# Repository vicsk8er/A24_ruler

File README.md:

# CCI UdeS A24_ruler  
Concours de Circuit Imprimé Université de Sherbrooke, automne 2024  
## Thème : règle

Bienvenue à la compétition de conception de PCB sur le thème "règle" ! Cette compétition vise à stimuler la créativité et l'innovation dans la conception de circuits imprimés en vous invitant à créer une souris d'ordinateur unique et fonctionnelle.

### Répertoire "Template"  
Le répertoire "Template" contient tous les documents à remplir pour participer à la compétition. Vous y trouverez :  
- Formulaire d'idée  
- Formulaire d'inscription  

Le répertoire contient également un "Template" pour vous aider lors de la création de la documentation :  
- TEMPLATES de documentation CCI  

### Répertoires code, elec et mech  
Chacun de ces répertoires contient de la documentation de départ pour vous guider. Consultez la section "doc". Ces répertoires sont également là pour vous aider à vous organiser lors du développement de votre règle.

### Comment forker le dépôt

1. Accédez au dépôt GitHub officiel à l'adresse suivante : `https://github.com/CCI-udes/A24_ruler`.
2. Cliquez sur le bouton "Fork" en haut à droite de la page du dépôt.
3. Sélectionnez votre propre compte GitHub comme destination du fork.
4. Clonez le dépôt forké sur votre machine locale en utilisant la commande suivante :
   ```bash
   git clone https://github.com/<votre-utilisateur>/A24_ruler.git
   ```

### Ressources supplémentaires

- Si vous avez des questions ou avez besoin d'aide, n'hésitez pas à nous contacter.
- Rejoignez notre canal Discord pour discuter avec d'autres participants et obtenir des conseils et des astuces.

Nous vous souhaitons bonne chance et avons hâte de voir vos créations !

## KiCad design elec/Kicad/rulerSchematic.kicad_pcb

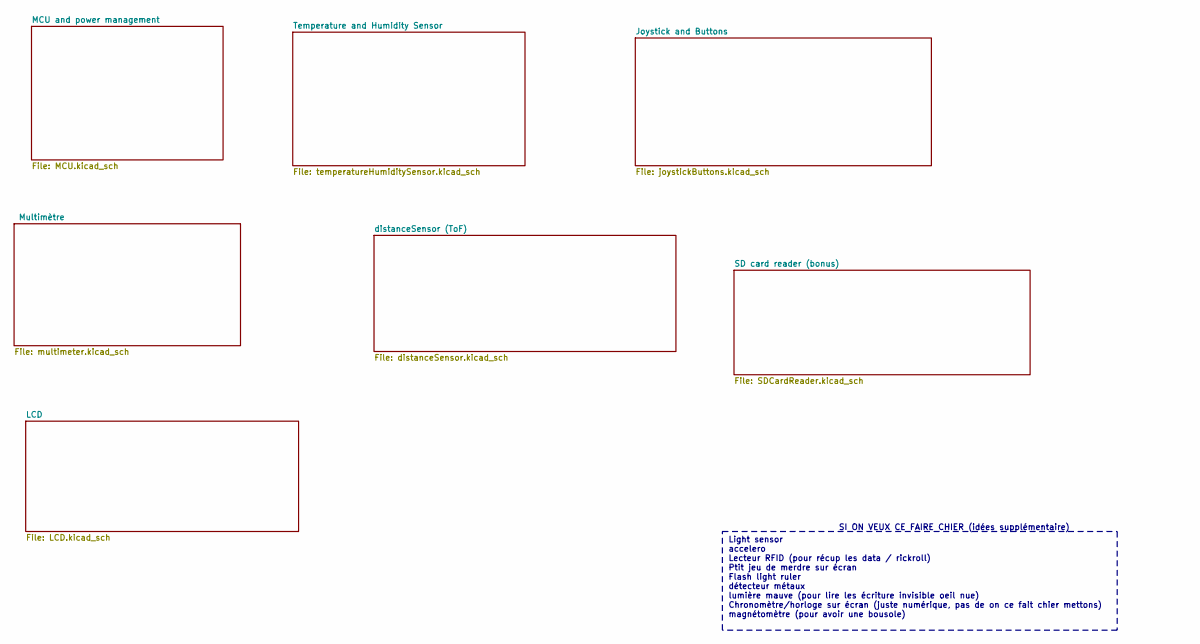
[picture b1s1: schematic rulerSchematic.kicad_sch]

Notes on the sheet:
Light sensor accelero Lecteur RFID (pour récup les data / rickroll) Ptit jeu de merdre sur écran Flash light ruler détecteur métaux lumière mauve (pour lire les écriture invisible oeil nue) Chronomètre/horloge sur écran (juste numérique, pas de on ce fait chier mettons) magnétomètre (pour avoir une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
SI ON VEUX CE FAIRE CHIER (idées supplémentaire)

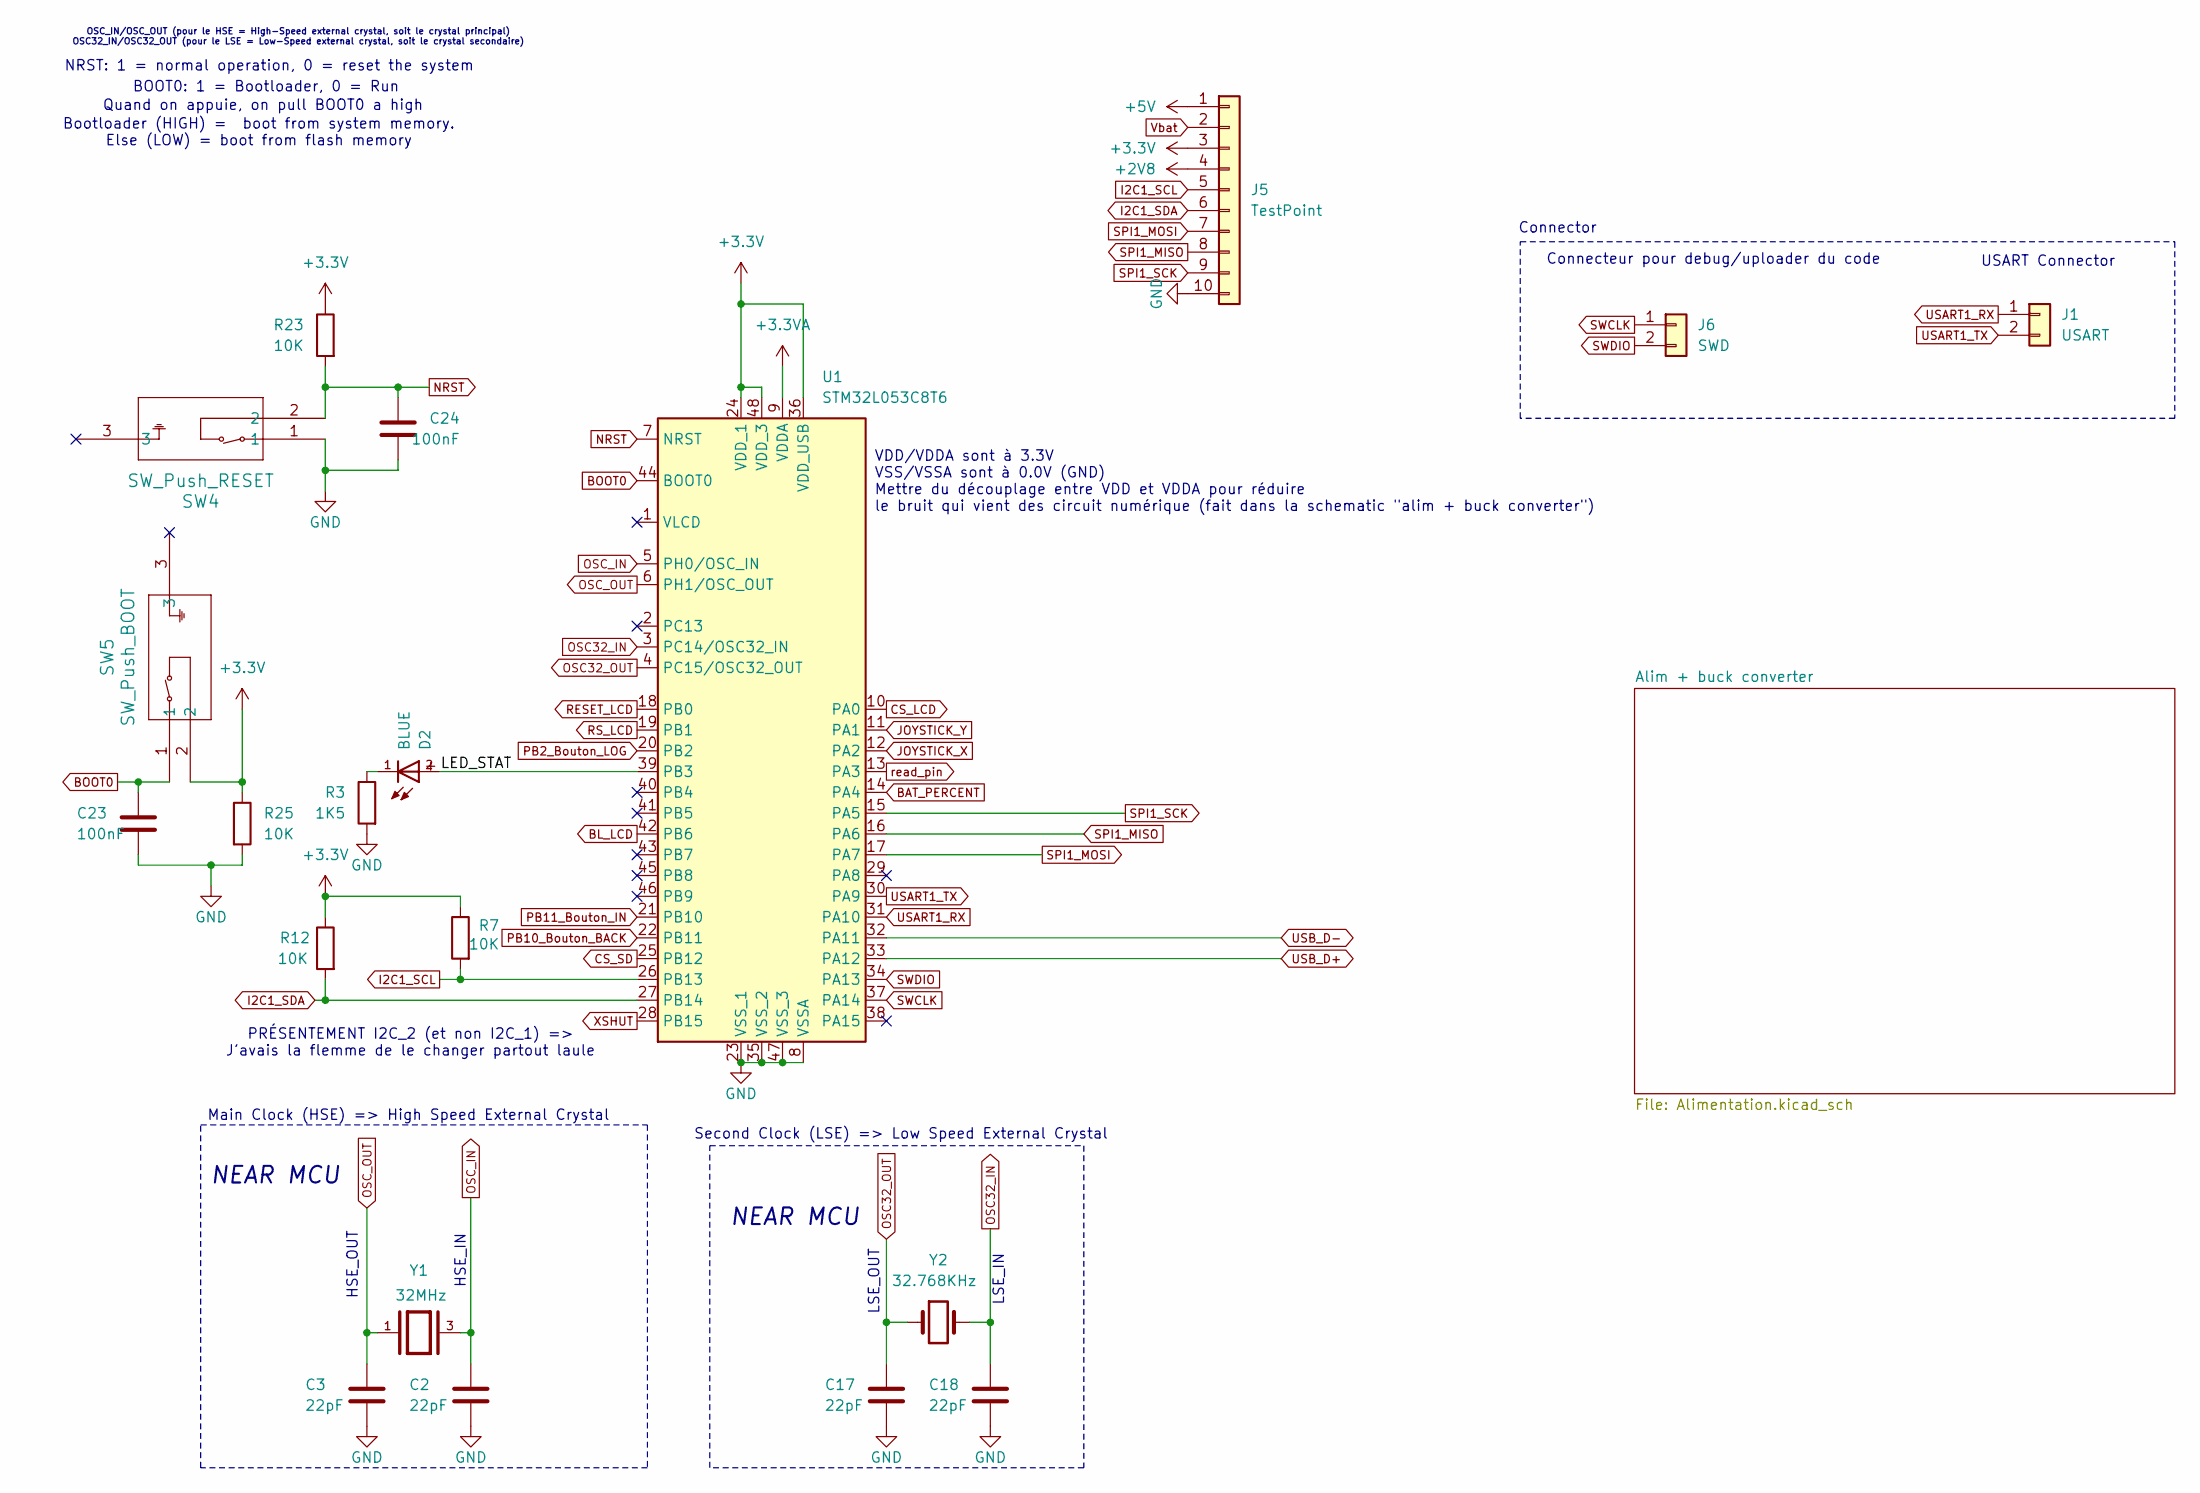
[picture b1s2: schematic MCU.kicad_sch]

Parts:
C2, C3, C17, C18: 22pF; C_0402_1005Metric_Pad0.74x0.62mm_HandSolder
C23, C24: 100nF; C_0402_1005Metric_Pad0.74x0.62mm_HandSolder
D2: BLUE; WL-SMCD_0603
J1: USART; PinHeader_1x02_P2.54mm_Vertical
J5: TestPoint; PinSocket_1x10_P2.54mm_Vertical
J6: SWD; PinHeader_1x02_P2.54mm_Vertical
R3: 1K5; R_0402_1005Metric_Pad0.72x0.64mm_HandSolder
R7, R12, R23, R25: 10K; R_0402_1005Metric_Pad0.72x0.64mm_HandSolder
SW4: SW_Push_RESET; B3U-1100P_OMR
SW5: SW_Push_BOOT; B3U-1100P_OMR
U1: STM32L053C8T6; LQFP-48_7x7mm_P0.5mm
Y1: 32MHz; OSC_XRCGB32M000F2P01R0; PARTREV N/A
Y2: 32.768KHz; Crystal_SMD_3215-2Pin_3.2x1.5mm

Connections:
+2V8: J5.4; also elsewhere on the board
+3.3V: J5.3, R7.1, R12.1, R23.1, R25.1, SW5.2, U1.24 (VDD_1), U1.36 (VDD_USB), U1.48 (VDD_3); also elsewhere on the board
+3.3VA: U1.9 (VDDA); also elsewhere on the board
+5V: J5.1; also elsewhere on the board
/MCU and power management/LED_STAT: D2.2, U1.39 (PB3)
BAT_PERCENT: U1.14 (PA4); also elsewhere on the board
BL_LCD: U1.42 (PB6); also elsewhere on the board
BOOT0: C23.1, SW5.1, U1.44 (BOOT0)
CS_LCD: U1.10 (PA0); also elsewhere on the board
CS_SD: U1.25 (PB12); also elsewhere on the board
GND: C2.2, C3.2, C17.2, C18.2, C23.2, C24.2, J5.10, R3.2, R25.2, SW4.1, U1.8 (VSSA), U1.23 (VSS_1), U1.35 (VSS_2), U1.47 (VSS_3); also elsewhere on the board
I2C1_SCL: J5.5, R7.2, U1.26 (PB13); also elsewhere on the board
I2C1_SDA: J5.6, R12.2, U1.27 (PB14); also elsewhere on the board
JOYSTICK_X: U1.12 (PA2); also elsewhere on the board
JOYSTICK_Y: U1.11 (PA1); also elsewhere on the board
NRST: C24.1, R23.2, SW4.2, U1.7 (NRST)
unnamed: D2.1, R3.1
OSC32_IN: C18.1, U1.3 (PC14/OSC32_IN), Y2.2
OSC32_OUT: C17.1, U1.4 (PC15/OSC32_OUT), Y2.1
OSC_IN: C2.1, U1.5 (PH0/OSC_IN), Y1.3
OSC_OUT: C3.1, U1.6 (PH1/OSC_OUT), Y1.1
PB2_Bouton_LOG: U1.20 (PB2); also elsewhere on the board
PB10_Bouton_BACK: U1.22 (PB11); also elsewhere on the board
PB11_Bouton_IN: U1.21 (PB10); also elsewhere on the board
RESET_LCD: U1.18 (PB0); also elsewhere on the board
RS_LCD: U1.19 (PB1); also elsewhere on the board
SPI1_MISO: J5.8, U1.16 (PA6); also elsewhere on the board
SPI1_MOSI: J5.7, U1.17 (PA7); also elsewhere on the board
SPI1_SCK: J5.9, U1.15 (PA5); also elsewhere on the board
SWCLK: J6.1, U1.37 (PA14)
SWDIO: J6.2, U1.34 (PA13)
USART1_RX: J1.1, U1.31 (PA10)
USART1_TX: J1.2, U1.30 (PA9)
USB_D+: U1.33 (PA12); also elsewhere on the board
USB_D-: U1.32 (PA11); also elsewhere on the board
Vbat: J5.2; also elsewhere on the board
XSHUT: U1.28 (PB15); also elsewhere on the board
read_pin: U1.13 (PA3); also elsewhere on the board

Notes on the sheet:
HSE_IN
BOOT0: 1 = Bootloader, 0 = Run
Connecteur pour debug/uploader du code
Main Clock (HSE) => High Speed External Crystal
Bootloader (HIGH) = boot from system memory. Else (LOW) = boot from flash memory
PRÉSENTEMENT I2C_2 (et non I2C_1) => J'avais la flemme de le changer partout laule
Second Clock (LSE) => Low Speed External Crystal
Quand on appuie, on pull BOOT0 a high
NEAR MCU
OSC_IN/OSC_OUT (pour le HSE = High-Speed external crystal, soit le crystal principal) OSC32_IN/OSC32_OUT (pour le LSE = Low-Speed external crystal, soit le crystal secondaire)
VDD/VDDA sont à 3.3V VSS/VSSA sont à 0.0V (GND) Mettre du découplage entre VDD et VDDA pour réduire le bruit qui vient des circuit numérique (fait dans la schematic "alim + buck converter")
Connector
NRST: 1 = normal operation, 0 = reset the system
USART Connector
LSE_IN
LSE_OUT
HSE_OUT

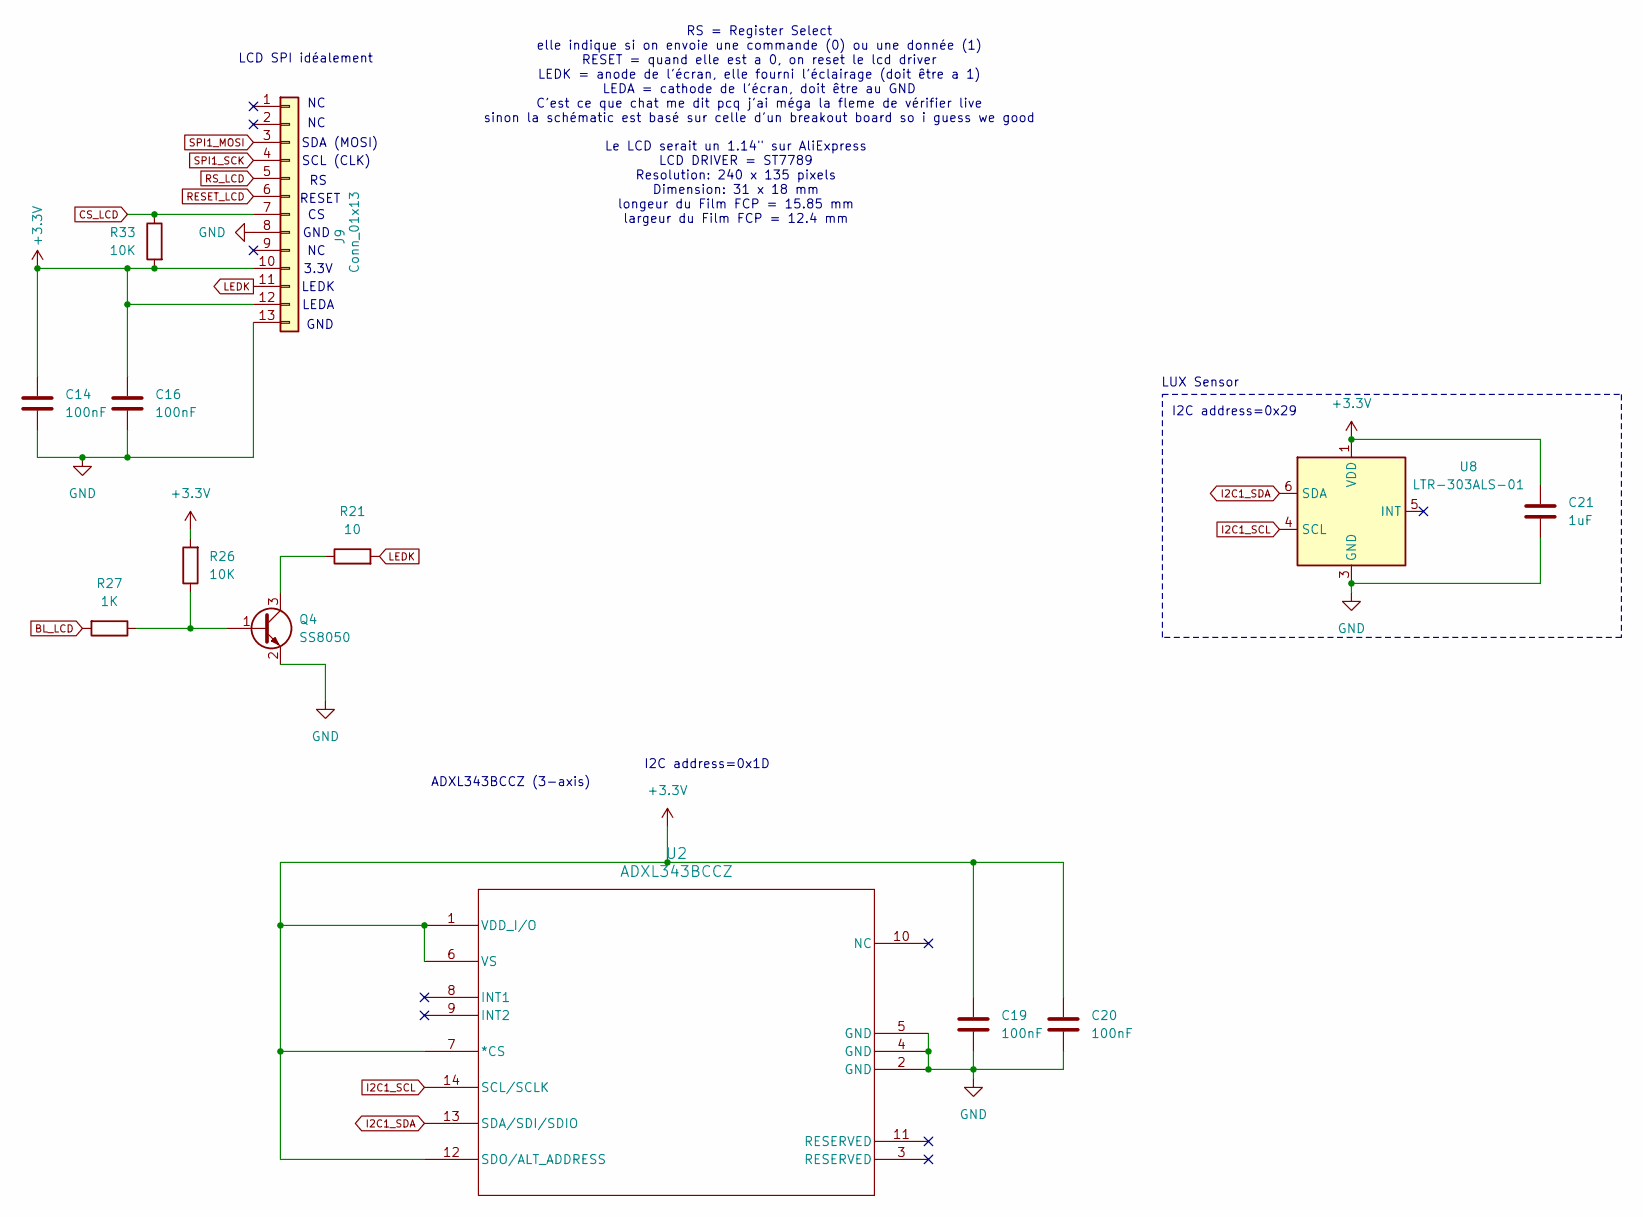
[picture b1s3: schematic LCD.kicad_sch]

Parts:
C14, C16, C19, C20: 100nF; C_0402_1005Metric_Pad0.74x0.62mm_HandSolder
C21: 1uF; C_0402_1005Metric_Pad0.74x0.62mm_HandSolder
J9: Conn_01x13; Hirose_FH12-13S-0.5SH_1x13-1MP_P0.50mm_Horizontal
Q4: SS8050; SOT-23
R21: 10; R_0402_1005Metric_Pad0.72x0.64mm_HandSolder
R26, R33: 10K; R_0402_1005Metric_Pad0.72x0.64mm_HandSolder
R27: 1K; R_0402_1005Metric_Pad0.72x0.64mm_HandSolder
U2: ADXL343BCCZ; LGA_CC-14-1_ADI
U8: LTR-303ALS-01; Lite-On_LTR-303ALS-01

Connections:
+3.3V: C14.1, C16.1, C19.1, C20.1, C21.1, J9.10, J9.12, R26.2, R33.2, U2.1 (VDD_I/O), U2.6 (VS), U2.7 (*CS), U2.12 (SDO/ALT_ADDRESS), U8.1 (VDD); also elsewhere on the board
BL_LCD: R27.2; also elsewhere on the board
CS_LCD: J9.7, R33.1; also elsewhere on the board
GND: C14.2, C16.2, C19.2, C20.2, C21.2, J9.8, J9.13, Q4.2 (E), U2.2 (GND), U2.4 (GND), U2.5 (GND), U8.3 (GND); also elsewhere on the board
I2C1_SCL: U2.14 (SCL/SCLK), U8.4 (SCL); also elsewhere on the board
I2C1_SDA: U2.13 (SDA/SDI/SDIO), U8.6 (SDA); also elsewhere on the board
LEDK: J9.11, R21.2
unnamed: Q4.1 (B), R26.1, R27.1
unnamed: Q4.3 (C), R21.1
RESET_LCD: J9.6; also elsewhere on the board
RS_LCD: J9.5; also elsewhere on the board
SPI1_MOSI: J9.3; also elsewhere on the board
SPI1_SCK: J9.4; also elsewhere on the board

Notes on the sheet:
RESET
LEDA
GND
LEDK
SCL (CLK)
LUX Sensor
ADXL343BCCZ (3-axis)
SDA (MOSI)
RS = Register Select elle indique si on envoie une commande (0) ou une donnée (1) RESET = quand elle est a 0, on reset le lcd driver LEDK = anode de l'écran, elle fourni l'éclairage (doit être a 1) LEDA = cathode de l'écran, doit être au GND C'est ce que chat me dit pcq j'ai méga la fleme de vérifi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
LCD SPI idéalement
I2C address=0x1D
3.3V
I2C address=0x29
Le LCD serait un 1.14" sur AliExpress LCD DRIVER = ST7789 Resolution: 240 x 135 pixels Dimension: 31 x 18 mm longeur du Film FCP = 15.85 mm largeur du Film FCP = 12.4 mm

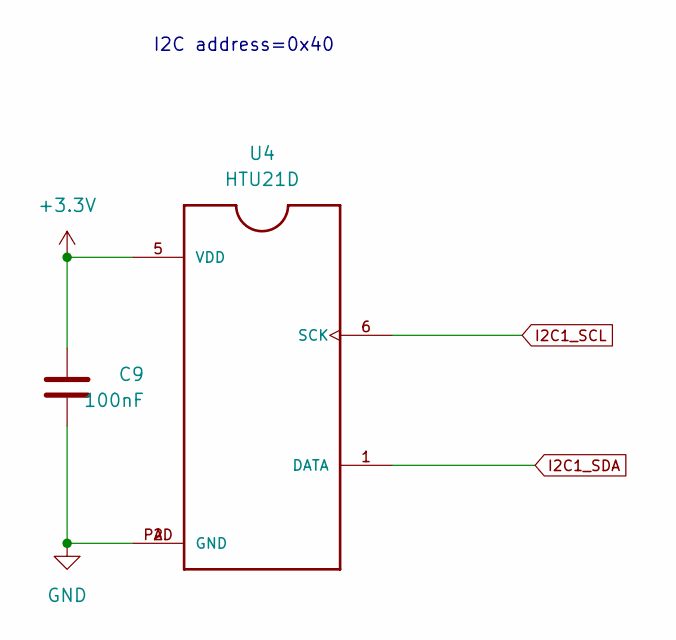
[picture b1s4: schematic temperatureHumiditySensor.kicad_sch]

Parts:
C9: 100nF; C_0402_1005Metric_Pad0.74x0.62mm_HandSolder
U4: HTU21D; QFN100P300X300X100-7N

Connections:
+3.3V: C9.1, U4.5 (VDD); also elsewhere on the board
GND: C9.2, U4.2 (GND), U4.PAD (GND); also elsewhere on the board
I2C1_SCL: U4.6 (SCK); also elsewhere on the board
I2C1_SDA: U4.1 (DATA); also elsewhere on the board

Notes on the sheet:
I2C address=0x40

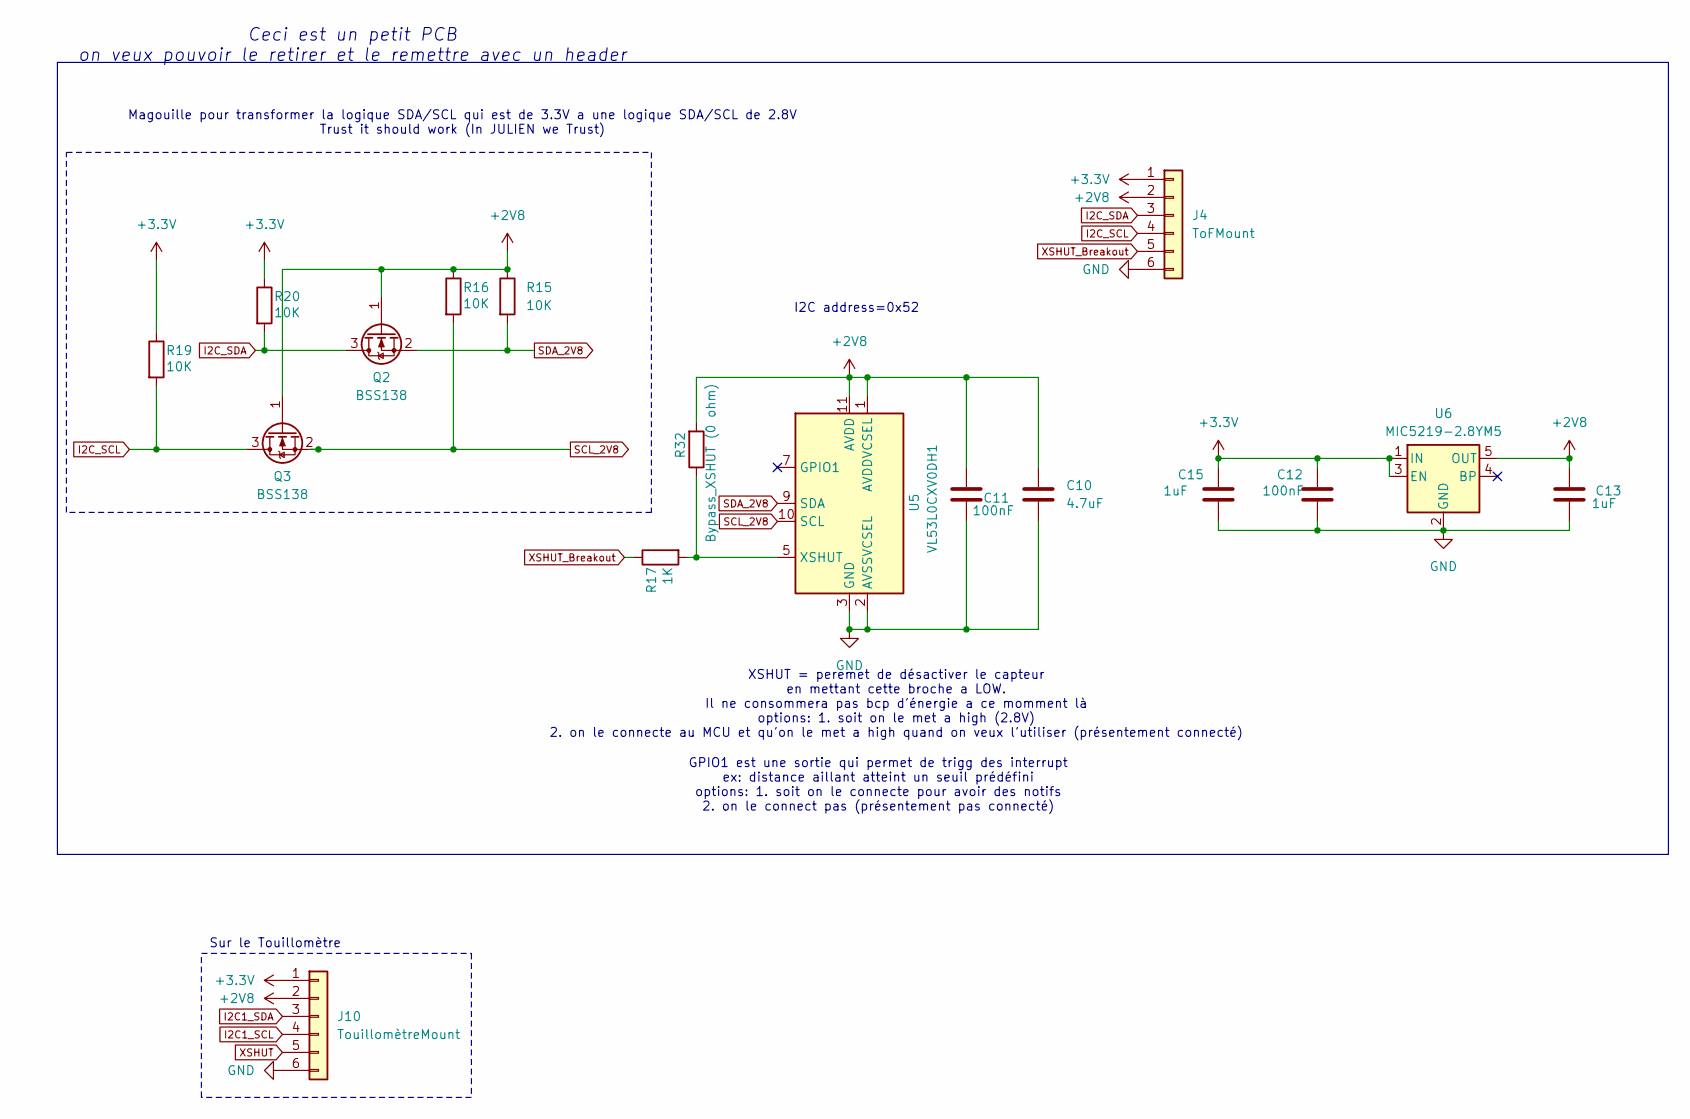
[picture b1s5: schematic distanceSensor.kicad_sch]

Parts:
C10: 4.7uF; C_0402_1005Metric_Pad0.74x0.62mm_HandSolder
C11, C12: 100nF; C_0402_1005Metric_Pad0.74x0.62mm_HandSolder
C13, C15: 1uF; C_0402_1005Metric_Pad0.74x0.62mm_HandSolder
J4: ToFMount; PinHeader_1x06_P2.54mm_Horizontal
J10: TouillomètreMount; PinSocket_1x06_P2.54mm_Vertical
Q2, Q3: BSS138; SOT-23
R15, R16, R19, R20: 10K; R_0402_1005Metric_Pad0.72x0.64mm_HandSolder
R17: 1K; R_0402_1005Metric_Pad0.72x0.64mm_HandSolder
R32: Bypass_XSHUT (0 ohm); R_0402_1005Metric_Pad0.72x0.64mm_HandSolder
U5: VL53L0CXV0DH1; ST_VL53L1x
U6: MIC5219-2.8YM5; SOT-23-5

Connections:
+2V8: C10.1, C11.1, C13.1, J4.2, J10.2, Q2.1 (G), Q3.1 (G), R15.1, R16.1, R32.2, U5.1 (AVDDVCSEL), U5.11 (AVDD), U6.5 (OUT); also elsewhere on the board
+3.3V: C12.1, C15.1, J4.1, J10.1, R19.1, R20.1, U6.1 (IN), U6.3 (EN); also elsewhere on the board
GND: C10.2, C11.2, C12.2, C13.2, C15.2, J4.6, J10.6, U5.2 (AVSSVCSEL), U5.3 (GND), U5.4 (GND), U5.6 (GND), U5.12 (GND), U6.2 (GND); also elsewhere on the board
I2C1_SCL: J10.4; also elsewhere on the board
I2C1_SDA: J10.3; also elsewhere on the board
I2C_SCL: J4.4, Q3.3 (D), R19.2
I2C_SDA: J4.3, Q2.3 (D), R20.2
unnamed: R17.2, R32.1, U5.5 (XSHUT)
SCL_2V8: Q3.2 (S), R16.2, U5.10 (SCL)
SDA_2V8: Q2.2 (S), R15.2, U5.9 (SDA)
XSHUT: J10.5; also elsewhere on the board
XSHUT_Breakout: J4.5, R17.1

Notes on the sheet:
I2C address=0x52
Magouille pour transformer la logique SDA/SCL qui est de 3.3V a une logique SDA/SCL de 2.8V Trust it should work (In JULIEN we Trust)
GPIO1 est une sortie qui permet de trigg des interrupt ex: distance aillant atteint un seuil prédéfini options: 1. soit on le connecte pour avoir des notifs 2. on le connect pas (présentement pas connecté)
Ceci est un petit PCB on veux pouvoir le retirer et le remettre avec un header
Sur le Touillomètre
XSHUT = peremet de désactiver le capteur en mettant cette broche a LOW. Il ne consommera pas bcp d'énergie a ce momment là options: 1. soit on le met a high (2.8V) 2. on le connecte au MCU et qu'on le met a high quand on veux l'utiliser (présentement connecté)

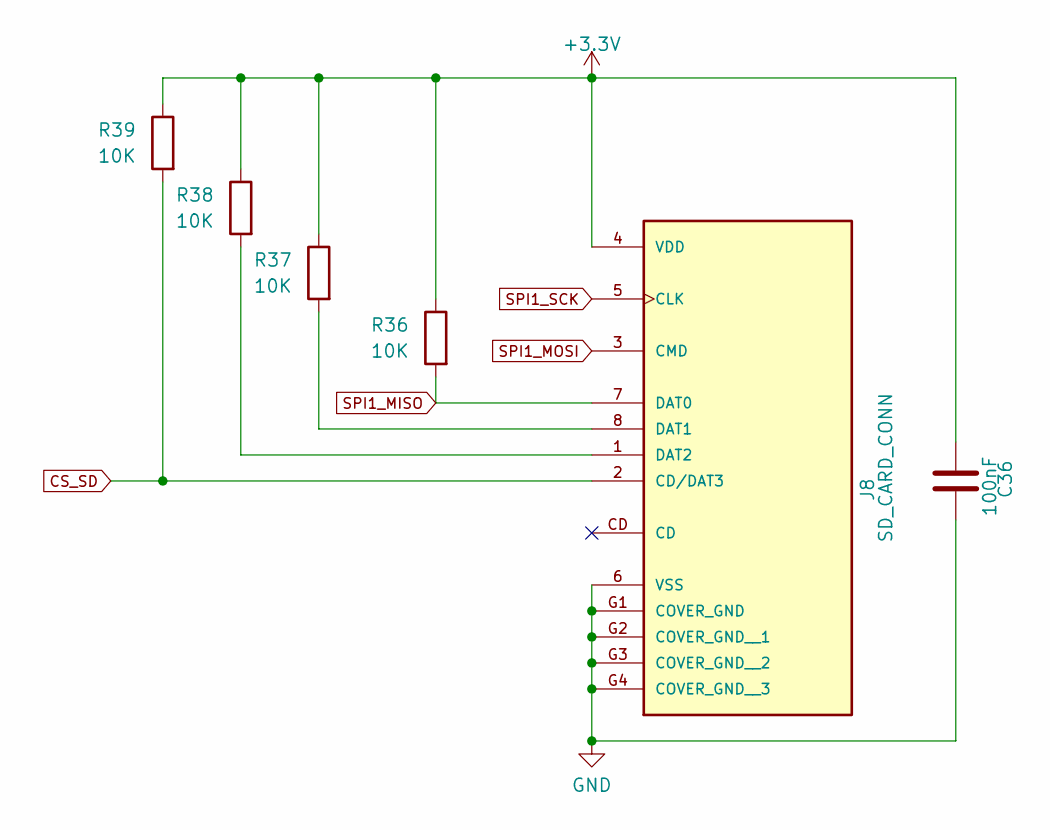
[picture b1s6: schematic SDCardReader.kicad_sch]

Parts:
C36: 100nF; C_0402_1005Metric_Pad0.74x0.62mm_HandSolder
J8: SD_CARD_CONN; CUI_MSD-4-A; PARTREV 1.0
R36, R37, R38, R39: 10K; R_0402_1005Metric_Pad0.72x0.64mm_HandSolder

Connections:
+3.3V: C36.1, J8.4 (VDD), R36.1, R37.1, R38.1, R39.1; also elsewhere on the board
CS_SD: J8.2 (CD/DAT3), R39.2; also elsewhere on the board
GND: C36.2, J8.6 (VSS), J8.G1 (COVER_GND), J8.G2 (COVER_GND__1), J8.G3 (COVER_GND__2), J8.G4 (COVER_GND__3); also elsewhere on the board
unnamed: J8.8 (DAT1), R37.2
unnamed: J8.1 (DAT2), R38.2
SPI1_MISO: J8.7 (DAT0), R36.2; also elsewhere on the board
SPI1_MOSI: J8.3 (CMD); also elsewhere on the board
SPI1_SCK: J8.5 (CLK); also elsewhere on the board

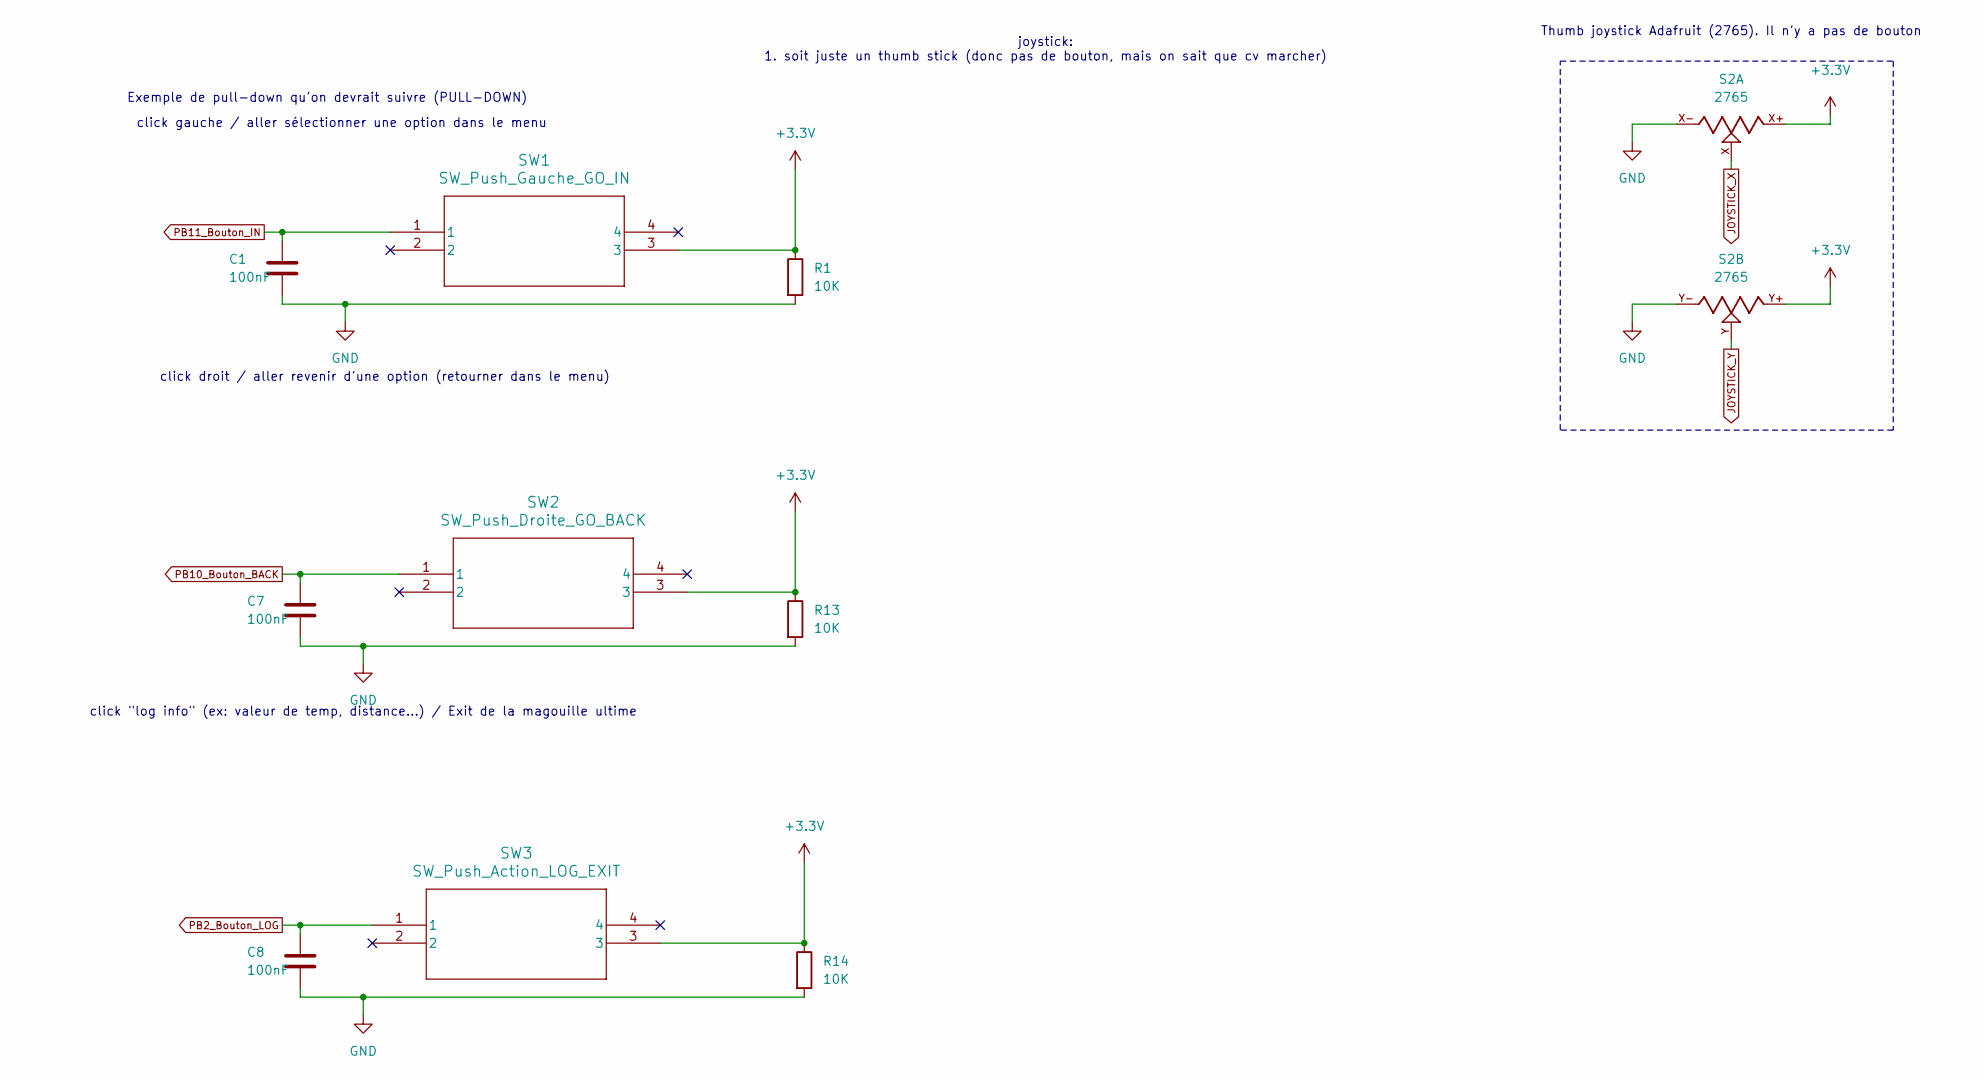
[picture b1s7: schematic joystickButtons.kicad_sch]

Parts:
C1, C7, C8: 100nF; C_0402_1005Metric_Pad0.74x0.62mm_HandSolder
R1, R13, R14: 10K; R_0402_1005Metric_Pad0.72x0.64mm_HandSolder
S2: 2765; SW_2765
SW1: SW_Push_Gauche_GO_IN; SWITCH_TR2LFS
SW2: SW_Push_Droite_GO_BACK; SWITCH_TR2LFS
SW3: SW_Push_Action_LOG_EXIT; SWITCH_TR2LFS

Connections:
+3.3V: R1.1, R13.1, R14.1, S2.X+, S2.Y+, SW1.3, SW2.3, SW3.3; also elsewhere on the board
GND: C1.2, C7.2, C8.2, R1.2, R13.2, R14.2, S2.X-, S2.Y-; also elsewhere on the board
JOYSTICK_X: S2.X; also elsewhere on the board
JOYSTICK_Y: S2.Y; also elsewhere on the board
PB2_Bouton_LOG: C8.1, SW3.1; also elsewhere on the board
PB10_Bouton_BACK: C7.1, SW2.1; also elsewhere on the board
PB11_Bouton_IN: C1.1, SW1.1; also elsewhere on the board

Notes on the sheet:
joystick: 1. soit juste un thumb stick (donc pas de bouton, mais on sait que cv marcher)
Thumb joystick Adafruit (2765). Il n'y a pas de bouton
Exemple de pull-down qu'on devrait suivre (PULL-DOWN)
click gauche / aller sélectionner une option dans le menu
click droit / aller revenir d'une option (retourner dans le menu)
click "log info" (ex: valeur de temp, distance...) / Exit de la magouille ultime

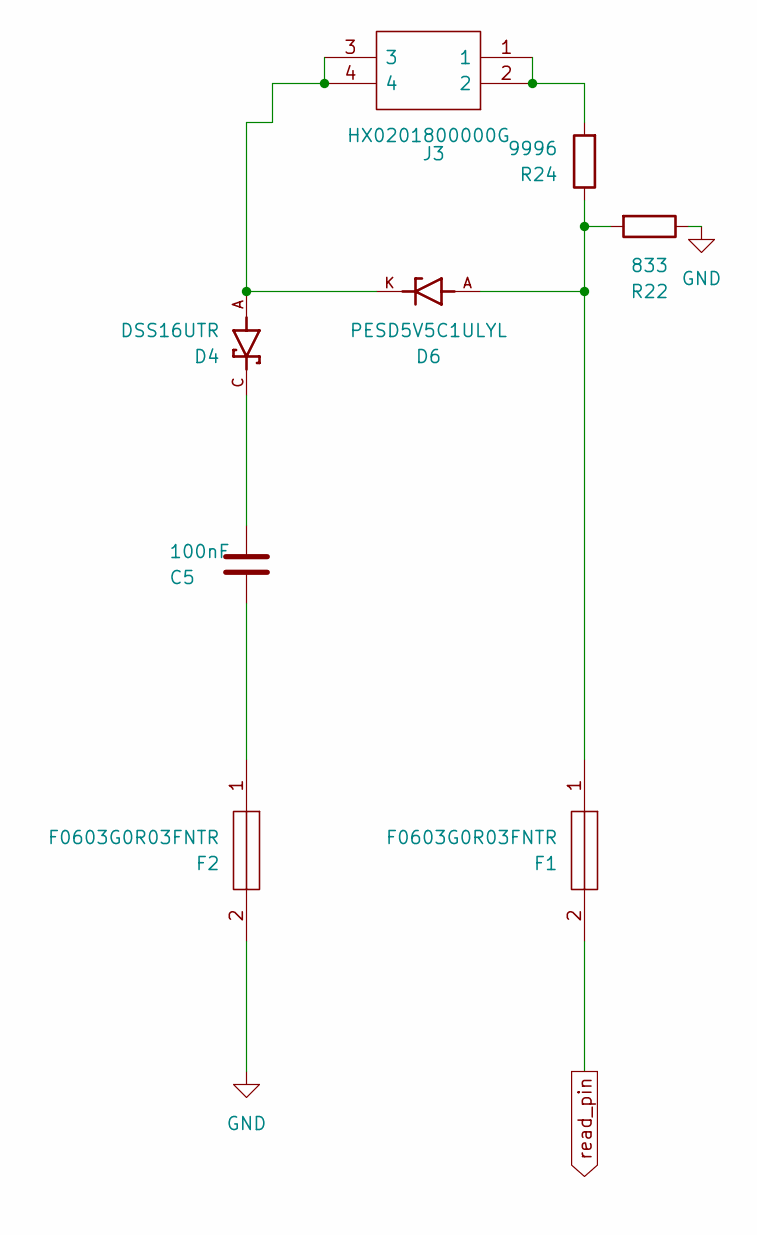
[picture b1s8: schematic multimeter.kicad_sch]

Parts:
C5: 100nF; C_0402_1005Metric_Pad0.74x0.62mm_HandSolder
D4: DSS16UTR; SODFL3618X110N
D6: PESD5V5C1ULYL; DIO_PESD5V5C1ULYL; PARTREV 6 April 2023
F1, F2: F0603G0R03FNTR; Mouser Part Number 581-F0603G0R03FNTR
J3: HX0201800000G; Mouser Part Number 649-HX02018000J0G
R22: 833; R_0402_1005Metric_Pad0.72x0.64mm_HandSolder
R24: 9996; R_0402_1005Metric_Pad0.72x0.64mm_HandSolder

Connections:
GND: F2.2, R22.1; also elsewhere on the board
unnamed: C5.1, F2.1
unnamed: C5.2, D4.C
unnamed: D4.A, D6.K, J3.3, J3.4
unnamed: D6.A, F1.1, R22.2, R24.1
unnamed: J3.1, J3.2, R24.2
read_pin: F1.2; also elsewhere on the board

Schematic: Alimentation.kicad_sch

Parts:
C25: 10uF; C_0402_1005Metric_Pad0.74x0.62mm_HandSolder
C26, C33, C35: 1uF; C_0402_1005Metric_Pad0.74x0.62mm_HandSolder
C27, C28, C29, C30, C32: 100nF; C_0402_1005Metric_Pad0.74x0.62mm_HandSolder
C34: 22uF; C_0402_1005Metric_Pad0.74x0.62mm_HandSolder
D1: GREEN; WL-SMCD_0603
D7: 1N4148WS; D_SOD-323
FB1: 100R; BEADC1608X65N
J7: USB_B_Micro_MAIN; USB_Micro-B_Amphenol_10103594-0001LF_Horizontal
L1: 27nH; INDC1005X55N
L2: 470nH; IND_VLS252012HBX-R47M-1
Q1: SI2323DS-T1; SOT-23
Q5: NTK3043NT1G; SOT40P120X55-3N; PARTREV 4
R2: 110K; R_0402_1005Metric_Pad0.72x0.64mm_HandSolder
R4, R11: 100; R_0402_1005Metric_Pad0.72x0.64mm_HandSolder
R5, R6: 300K; R_0402_1005Metric_Pad0.72x0.64mm_HandSolder
R10: 10K; R_0402_1005Metric_Pad0.72x0.64mm_HandSolder
R18: Bypass_MOSFET (0 ohm); R_0201_0603Metric
R28: 510K; R_0402_1005Metric_Pad0.72x0.64mm_HandSolder
R29: 162K; R_0402_1005Metric_Pad0.72x0.64mm_HandSolder
R30: 1M; R_0402_1005Metric_Pad0.72x0.64mm_HandSolder
R31: 1K5; R_0402_1005Metric_Pad0.72x0.64mm_HandSolder
S1: SW_ON/OFF; SW_DS04-254-2-01BK-SMT; PARTREV V0.0
U9: TLV62085RLTR; RLT0007A

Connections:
+3.3V: C26.1, C27.1, C28.1, C29.1, C30.1, C34.1, D1.2, L1.1, L2.2, R28.1, R30.1, U9.4 (VOS); also elsewhere on the board
+3.3VA: C32.1, C33.1, L1.2; also elsewhere on the board
+5V: FB1.1, J7.1 (VBUS); also elsewhere on the board
BAT_PERCENT: Q5.2, R5.2, R18.1; also elsewhere on the board
GND: C25.2, C26.2, C27.2, C28.2, C29.2, C30.2, C32.2, C33.2, C34.2, C35.2, J7.5 (GND), J7.6 (Shield), R5.1, R6.2, R10.1, R29.2, R31.2, U9.5 (GND); also elsewhere on the board
unnamed: D1.1, R31.1
unnamed: D7.1 (K), Q1.3 (D), S1.1A
unnamed: Q1.1 (G), R11.1
unnamed: Q5.1, R4.2
unnamed: Q5.3, R2.1, R18.2
unnamed: R28.2, R29.1, U9.3 (FB)
unnamed: R30.2, U9.2 (PG)
unnamed: L2.1, U9.6 (SW)
USB_D+: J7.3 (D+); also elsewhere on the board
USB_D-: J7.2 (D-); also elsewhere on the board
Vbat: Q1.2 (S), R2.2; also elsewhere on the board
Vin: C25.1, R4.1, R6.1, S1.1B, U9.1 (EN), U9.7 (VIN)
VinBat: C35.1, D7.2 (A), FB1.2, R10.2, R11.2; also elsewhere on the board

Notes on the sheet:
passe bas pour filtrer VDDA
Vin = 5V Vbat = entre 4.2V et 3.5V
Régulateur tension 3.3V (input: 5V-3.4V)
Si ça scrap, on enlève la resistance + mosfet et on soude le bridge
Découplage entre VDD et VDDA pour réduire le bruit au maximum
In Phil we Trust
METTRE DES SWITCH POUR ÉTEINDRE LE CIRCUIT + avoir une scroll wheel vrm bs pour les menu (et la magouille ultime)
Battery percentage charger
Quand Vbat = 3.5V, BAT_PERCENT = 2.55V Quand Vbat = 4.2V, BAT_PERCENT = 3.07V
LED QUI INDIQUE QUE LE CIRCUIT EST ALIMENTÉ
La valeur de la res pour la DEL est haute(1K5), mais normal selon Phil's Lab
N-Channel
NEAR MCU
MOSFET P-Channel: Si une tension appliqué a la Gate est inférieur a celle de la Source, le courant va circuler de la Source au Drain
MOSFET N-Channel: Si une tension appliqué a la Gate est suppérieur que celle a la Source, le courant va circuler du Drain a la Source
P-Channel

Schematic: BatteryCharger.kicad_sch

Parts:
C4, C6: 4.7uF; C_0402_1005Metric_Pad0.74x0.62mm_HandSolder
D3: RED; WL-SMCD_0603
H1, H2, H3, H4: MountingHole; MountingHole_2.2mm_M2
J2: S2B-XH-A; JST_XH_S2B-XH-A_1x02_P2.50mm_Horizontal; PARTREV N/A
R8: 470; R_0402_1005Metric_Pad0.72x0.64mm_HandSolder
R9: 2K; R_0402_1005Metric_Pad0.72x0.64mm_HandSolder
U3: MCP73831; SOT-23-5

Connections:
GND: C4.2, C6.2, J2.1, R9.2, U3.2 (V_{SS}); also elsewhere on the board
unnamed: D3.1, R8.1
unnamed: R9.1, U3.5 (PROG)
unnamed: R8.2, U3.1 (STAT)
Vbat: C6.1, J2.2, U3.3 (V_{BAT}); also elsewhere on the board
VinBat: C4.1, D3.2, U3.4 (V_{DD}); also elsewhere on the board

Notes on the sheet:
Charging circuit
Mounting Hole Battery + LCD
LED qui indique que la battery recharge
M2 Screw
Valider si j'ai pas inverser les connexion ici du connecteur de la batterie
Charging at 4.2V with 500mA current

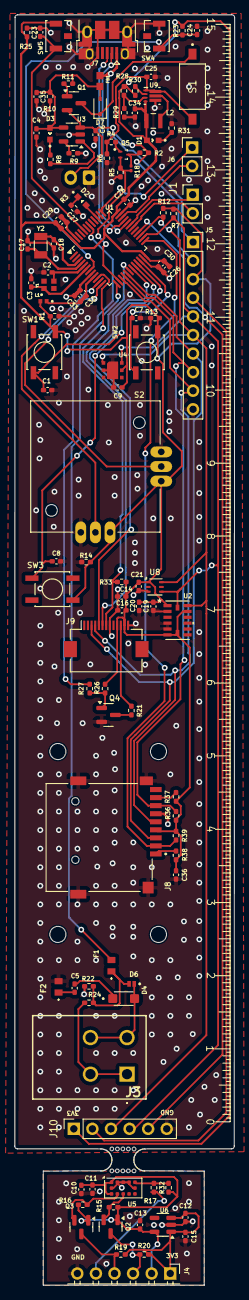
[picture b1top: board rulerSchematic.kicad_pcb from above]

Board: 2 copper layers, 30.1 x 173.7 mm, 119 parts (1 on the bottom side), 67 nets.

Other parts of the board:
mouse-bite-3mm-slot: VAL**; mouse-bite-3mm-slot

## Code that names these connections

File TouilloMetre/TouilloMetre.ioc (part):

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Mcu.Name=STM32L053C(6-8)Tx
Mcu.Package=LQFP48
Mcu.UserName=STM32L053C8Tx
PA0.GPIOParameters=GPIO_Speed,PinState,GPIO_PuPd,GPIO_Label
PA0.GPIO_Label=ST7789_CS
PA0.GPIO_PuPd=GPIO_PULLUP
PA0.GPIO_Speed=GPIO_SPEED_FREQ_LOW
PA0.PinState=GPIO_PIN_SET
PA0.Signal=GPIO_Output
PA1.Mode=IN1
PA1.Signal=ADC_IN1
PA10.Mode=Asynchronous
PA10.Signal=USART1_RX
PA11.Mode=Device
PA11.Signal=USB_DM
PA12.Mode=Device
PA12.Signal=USB_DP
PA13.Mode=Serial_Wire
PA13.Signal=SYS_SWDIO
PA14.Mode=Serial_Wire
PA14.Signal=SYS_SWCLK
PA2.Mode=IN2
PA2.Signal=ADC_IN2
PA3.Mode=IN3
PA3.Signal=ADC_IN3
PA4.Mode=IN4
PA4.Signal=ADC_IN4
PA5.GPIOParameters=GPIO_PuPd
PA5.GPIO_PuPd=GPIO_PULLUP
PA5.Mode=Full_Duplex_Master
PA5.Signal=SPI1_SCK
PA6.GPIOParameters=GPIO_PuPd
PA6.GPIO_PuPd=GPIO_PULLUP
PA6.Mode=Full_Duplex_Master
PA6.Signal=SPI1_MISO
PA7.GPIOParameters=GPIO_PuPd
PA7.GPIO_PuPd=GPIO_PULLUP
PA7.Mode=Full_Duplex_Master
PA7.Signal=SPI1_MOSI
PA9.Mode=Asynchronous
PA9.Signal=USART1_TX
PB0.GPIOParameters=GPIO_Label
PB0.GPIO_Label=ST7789_RESET
PB0.Signal=GPIO_Output
PB1.GPIOParameters=GPIO_Label
PB1.GPIO_Label=ST7789_RST
PB1.Signal=GPIO_Output
PB10.GPIOParameters=GPIO_Label
PB10.GPIO_Label=BOUTON_IN
PB10.Signal=GPIO_Input
PB11.GPIOParameters=GPIO_Label
PB11.GPIO_Label=BOUTON_BACK
PB11.Signal=GPIO_Input
PB12.GPIOParameters=PinState,GPIO_PuPd,GPIO_Label
PB12.GPIO_Label=SD_CS
PB12.GPIO_PuPd=GPIO_PULLUP
PB12.PinState=GPIO_PIN_SET
PB12.Signal=GPIO_Output
PB13.Mode=I2C
PB13.Signal=I2C2_SCL
PB14.Mode=I2C
PB14.Signal=I2C2_SDA
PB15.GPIOParameters=GPIO_Label
PB15.GPIO_Label=XSHUT
PB15.Signal=GPIO_Output
PB2.GPIOParameters=GPIO_Label
PB2.GPIO_Label=BOUTON_LOG
PB2.Signal=GPIO_Input
PB3.GPIOParameters=GPIO_Label
PB3.GPIO_Label=LED_STAT
PB3.Signal=GPIO_Output
PB6.GPIOParameters=GPIO_Label
PB6.GPIO_Label=ST7789_DC
PB6.Signal=GPIO_Output
PC14-OSC32_IN.Mode=LSE-External-Oscillator
PC14-OSC32_IN.Signal=RCC_OSC32_IN
PC15-OSC32_OUT.Mode=LSE-External-Oscillator
PC15-OSC32_OUT.Signal=RCC_OSC32_OUT
PH0-OSC_IN.Mode=HSE-External-Oscillator
PH0-OSC_IN.Signal=RCC_OSC_IN
PH1-OSC_OUT.Mode=HSE-External-Oscillator
PH1-OSC_OUT.Signal=RCC_OSC_OUT
RCC.HSE_VALUE=8000000
RCC.SYSCLKFreq_VALUE=32000000
RCC.SYSCLKSource=RCC_SYSCLKSOURCE_PLLCLK
board=custom

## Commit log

2024-09-09 1er push
2024-09-11 ajout d'exemple
2024-09-11 upload doc
2024-09-11 knowledge
2024-09-11 changement de date
2024-09-19 atelier 1
2024-09-27 first push on elec branch
2024-09-27 add the MCU and embedded deboger footprint in the schematic
2024-09-28 add the MCU and embedded debuger footprint in the schematic
2024-09-29 add the voltage regulator circuit and the decoupling circuit for VDD/VDDA
2024-09-30 did some change (but i have to verify them)
2024-10-07 boot/reset button
2024-10-15 merci Linux
2024-10-15 start the battery managemennt
2024-10-20 Presque finin la la gestion de la batterie (faire les dels demains)
2024-10-21 sa progresse. Battery management fini + humidity/temp sensor + bouton
2024-10-21 ta grand-maman
2024-10-21 oppsi
2024-10-22 merci charles de m'aider a nous aider
2024-10-22 multimetring
2024-10-24 multimetrie
2024-10-25 push pour charles (début de l'ajout diviseur tension pour la batterie)
2024-10-25 push de magouille pour charles
2024-10-25 j'ai fait l'écran
2024-10-26 ajout de la LSE
2024-10-26 manque h-bridge
2024-10-26 va falloir faire le PCB soon
2024-10-31 add a solder jumper on USB_D+ line in case we need it
2024-11-02 add a few footprint
2024-11-03 add a few footprints
2024-11-03 modif pour charly
2024-11-03 j'ai git force push laule
2024-11-03 formation torture
2024-11-03 J'ai ajouter des power Flag pour spécifier a Kicad que c'est chill (faut qu'il apprenne a ce géré quand même)
2024-11-03 ajout d'un Mosfet de type N pour pouvoir gérer le % de batterie (ADC)
2024-11-03 quick push
2024-11-04 commencer le PCB vite fait
2024-11-04 multimetre final
2024-11-05 touillerie
2024-11-05 igfukhj.hlk
2024-11-06 Jpense pas boire jeudi sérieux vue que y'a pas de 5@8
    routage du découplage et des CLK
2024-11-06 bloatware
    fait le slikscree de mesure (merci jabooby)
2024-11-06 sorry Jacob tu va être dessus ...
2024-11-07 modification du magnéto
2024-11-09 abdel aziz clutch l'app5
2024-11-09 j'essaye de fix la hauteur des designator pis si sa scrap cv être ça
2024-11-09 je vais au costco tantot i guess que c'est chill
2024-11-10 jpense qu'on est ready to order
2024-11-11 generated gerber files
2024-11-12 gruiter
2024-12-27 généré la schematic
2024-12-27 push pour charles
2024-12-27 added Menu class and dependencies
2024-12-27 j'ai rajouter une chier de choses
2024-12-28 truss it work on my machine
2024-12-28 everything works perfectly
